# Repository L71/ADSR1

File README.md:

ADSR1
=====

Eurorack digitally controlled ADSR envelope generator.

*** Deprecated (for now at least). 
It works more or less as intended on a breadboard but it got replaced by the ADSR2 module which does more or less the same things but with no MCU.

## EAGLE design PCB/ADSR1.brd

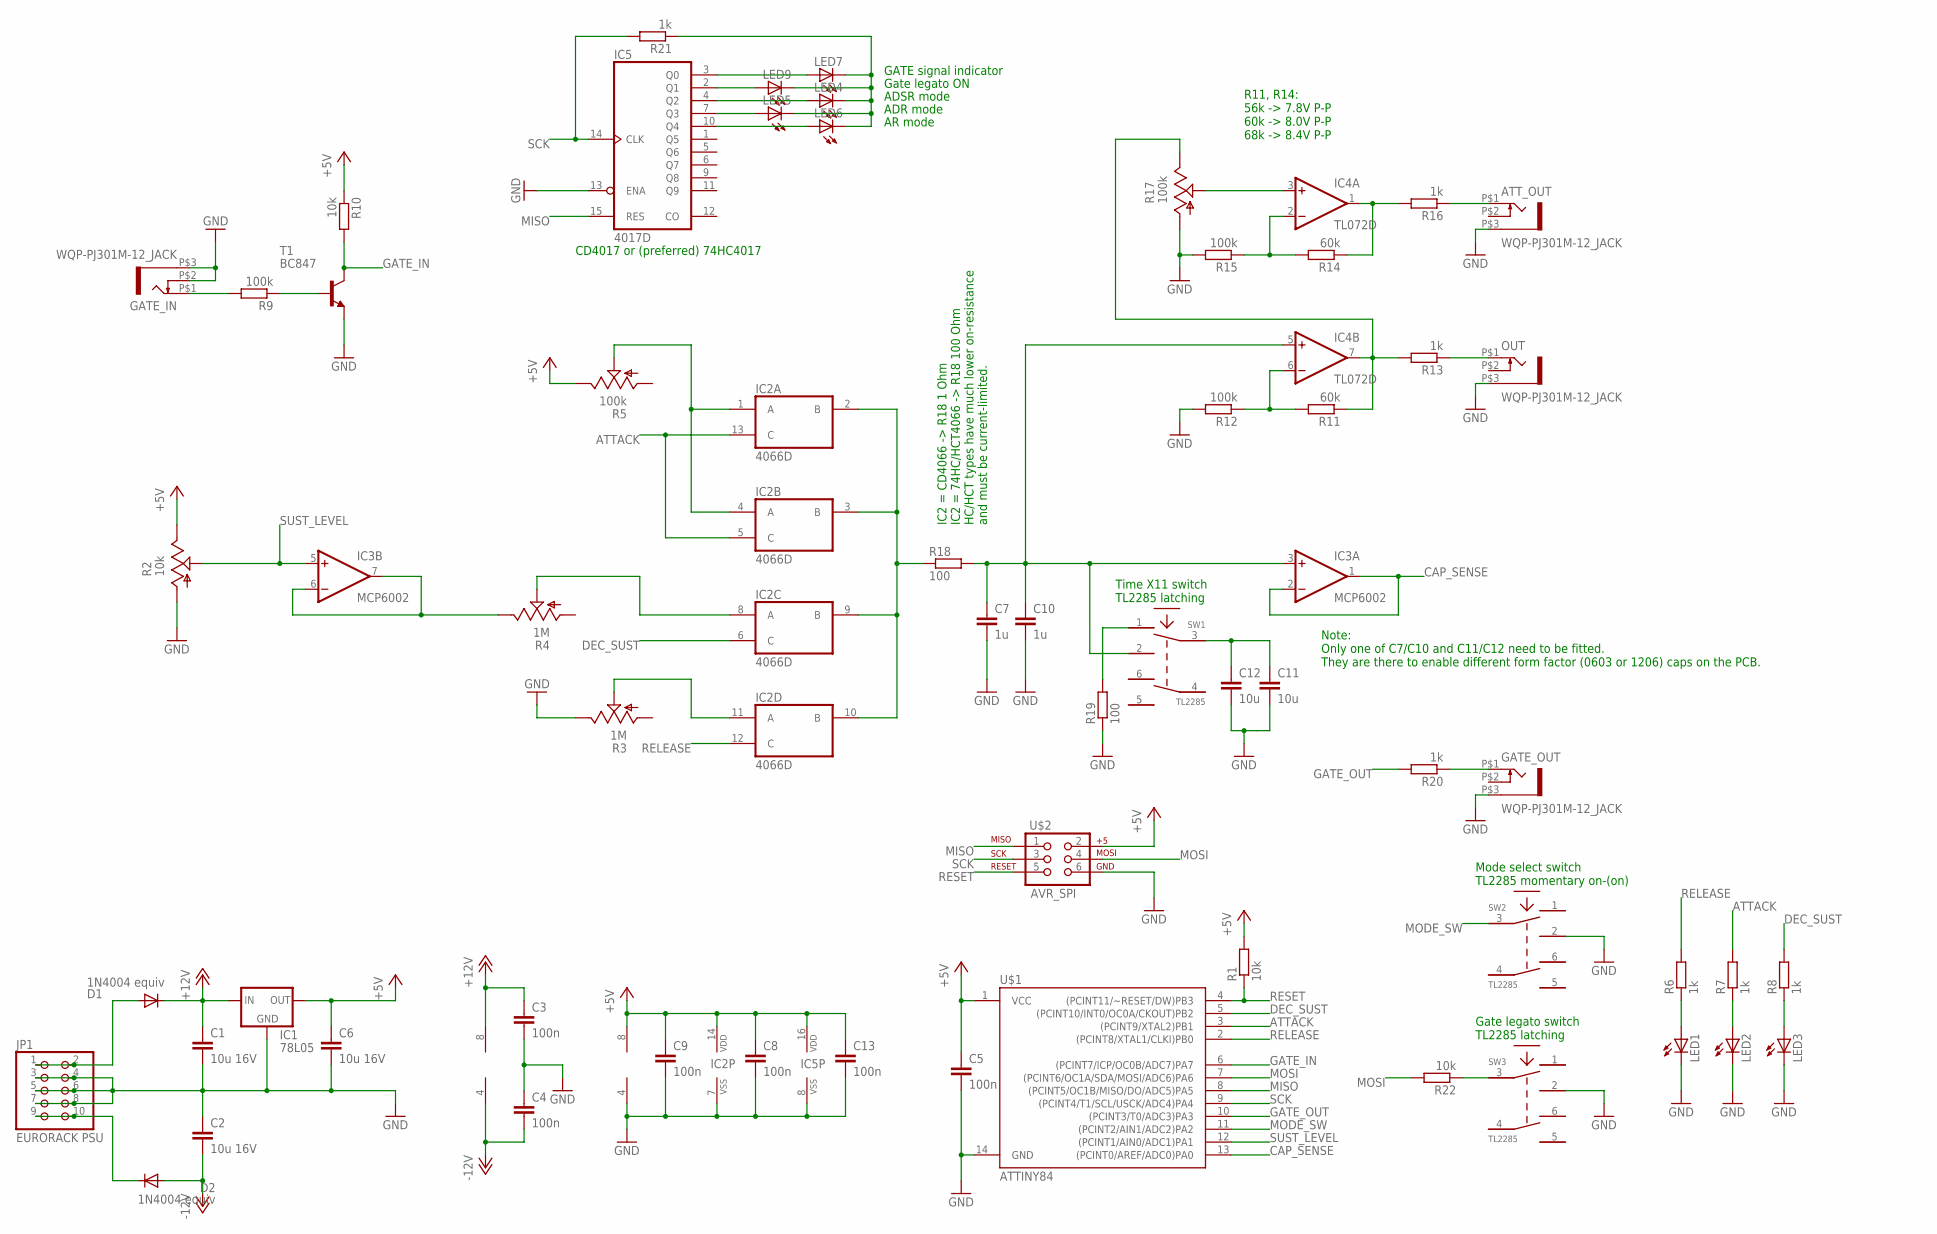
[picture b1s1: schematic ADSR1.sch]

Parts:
ATT_OUT: WQP-PJ301M-12_JACK
C1, C2, C6: 10u 16V; C1206K
C3, C4, C5, C8, C9, C13: 100n; C0603K
C7: 1u; C0603K
C10: 1u; C1206K
C11: 10u; C1206K
C12: 10u; C0603K
D1, D2: 1N4004 equiv; DO214AA
GATE_IN: WQP-PJ301M-12_JACK
GATE_OUT: WQP-PJ301M-12_JACK
IC1: 78L05; SOT89R
IC2: 4066D; SO14
IC3: MCP6002; SO08
IC4: TL072D; SO08
IC5: 4017D; SO16
JP1: EURORACK PSU; 2X05
LED1, LED2, LED3, LED4, LED5, LED6, LED7, LED9: LED3MM
OUT: WQP-PJ301M-12_JACK
R1, R10, R22: 10k; R0603
R2: 10k; ALPS_POT_VERTICAL
R3, R4: 1M; ALPS_POT_VERTICAL
R5, R17: 100k; ALPS_POT_VERTICAL
R6, R7, R8, R13, R16, R20, R21: 1k; R0603
R9, R12, R15: 100k; R0603
R11, R14: 60k; R0603
R18, R19: 100; R1206
SW1, SW2, SW3: TL2285; TL2285_PCB
T1: BC847; SOT23
U$1: ATTINY84; SO14
U$2: AVR_SPI; 2X3

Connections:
+5V: C5.1, C6.1, C8.1, C9.1, C13.1, IC1.PAD1 (OUT), IC2.14 (VDD), IC3.8 (V+), IC5.16 (VDD), R1.2, R2.P$1 (E), R5.P$1 (E), R10.1, U$1.1 (VCC), U$2.2
+12V: C1.1, C3.1, D1.C, IC1.PAD3 (IN), IC4.8 (V+)
-12V: C2.2, C4.2, D2.A, IC4.4 (V-)
ATTACK: IC2.5 (C), IC2.13 (C), R7.2, U$1.3 ((PCINT9/XTAL2)PB1)
CAP_SENSE: IC3.1 (OUT), IC3.2 (-IN), U$1.13 ((PCINT0/AREF/ADC0)PA0)
DEC_SUST: IC2.6 (C), R8.2, U$1.5 ((PCINT10/INT0/OC0A/CKOUT)PB2)
GATE_IN: R10.2, T1.3 (C), U$1.6 ((PCINT7/ICP/OC0B/ADC7)PA7)
GATE_OUT: R20.2, U$1.10 ((PCINT3/T0/ADC3)PA3)
GND: ATT_OUT.P$3 (1), C1.2, C2.1, C3.2, C4.1, C5.2, C6.2, C7.2, C8.2, C9.2, C10.2, C11.2, C12.2, C13.2, GATE_IN.P$2 (3), GATE_IN.P$3 (1), GATE_OUT.P$3 (1), IC1.PAD2 (GND), IC1.PAD4 (GND), IC2.7 (VSS), IC3.4 (V-), IC5.8 (VSS), IC5.13 (ENA), JP1.3, JP1.4, JP1.5, JP1.6, JP1.7, JP1.8, LED1.K (C), LED2.K (C), LED3.K (C), OUT.P$3 (1), R2.P$3 (A), R3.P$1 (E), R12.2, R15.2, R17.P$3 (A), R19.1, SW2.2, SW3.2, T1.2 (E), U$1.14 (GND), U$2.6
MISO: IC5.15 (RES), U$1.8 ((PCINT5/OC1B/MISO/DO/ADC5)PA5), U$2.1
MODE_SW: SW2.3, U$1.11 ((PCINT2/AIN1/ADC2)PA2)
MOSI: R22.2, U$1.7 ((PCINT6/OC1A/SDA/MOSI/ADC6)PA6), U$2.4
unnamed: C7.1, C10.1, IC3.3 (+IN), IC4.5 (+IN), R18.2, SW1.2
unnamed: GATE_IN.P$1 (2), R9.2
unnamed: D1.A, JP1.1, JP1.2
unnamed: LED3.A, R8.1
unnamed: IC2.11 (A), R3.P$2 (S)
unnamed: IC2.8 (A), R4.P$2 (S)
unnamed: IC3.6 (-IN), IC3.7 (OUT), R4.P$1 (E)
unnamed: LED2.A, R7.1
unnamed: LED1.A, R6.1
unnamed: IC2.1 (A), IC2.4 (A), R5.P$2 (S)
unnamed: OUT.P$1 (2), R13.1
unnamed: IC4.6 (-IN), R11.2, R12.1
unnamed: R9.1, T1.1 (B)
unnamed: D2.C, JP1.9, JP1.10
unnamed: IC4.7 (OUT), R11.1, R13.2, R17.P$1 (E)
unnamed: C11.1, C12.1, SW1.3
unnamed: IC2.2 (B), IC2.3 (B), IC2.9 (B), IC2.10 (B), R18.1
unnamed: R19.2, SW1.1
unnamed: ATT_OUT.P$1 (2), R16.1
unnamed: IC4.1 (OUT), R14.1, R16.2
unnamed: IC4.2 (-IN), R14.2, R15.1
unnamed: IC5.2 (Q1), LED9.A
unnamed: GATE_OUT.P$1 (2), R20.1
unnamed: IC4.3 (+IN), R17.P$2 (S)
unnamed: IC5.4 (Q2), LED4.A
unnamed: IC5.7 (Q3), LED5.A
unnamed: IC5.10 (Q4), LED6.A
unnamed: LED4.K (C), LED5.K (C), LED6.K (C), LED7.K (C), LED9.K (C), R21.1
unnamed: IC5.3 (Q0), LED7.A
unnamed: R22.1, SW3.3
RELEASE: IC2.12 (C), R6.2, U$1.2 ((PCINT8/XTAL1/CLKI)PB0)
RESET: R1.1, U$1.4 ((PCINT11/~RESET/DW)PB3), U$2.5
SCK: IC5.14 (CLK), R21.2, U$1.9 ((PCINT4/T1/SCL/USCK/ADC4)PA4), U$2.3
SUST_LEVEL: IC3.5 (+IN), R2.P$2 (S), U$1.12 ((PCINT1/AIN0/ADC1)PA1)

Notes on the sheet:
R11, R14: 56k -> 7.8V P-P 60k -> 8.0V P-P 68k -> 8.4V P-P
Time X11 switch TL2285 latching
IC2 = CD4066 -> R18 1 Ohm IC2 = 74HC/HCT4066 -> R18 100 Ohm HC/HCT types have much lower on-resistance and must be current-limited.
Note: Only one of C7/C10 and C11/C12 need to be fitted. They are there to enable different form factor (0603 or 1206) caps on the PCB.
Mode select switch TL2285 momentary on-(on)
GATE signal indicator
ADSR mode
ADR mode
AR mode
CD4017 or (preferred) 74HC4017
Gate legato switch TL2285 latching
Gate legato ON

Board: 2 copper layers, 61 parts (0 on the bottom side), 46 nets, no tracks yet.

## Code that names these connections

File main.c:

#define F_CPU 8000000UL

#include <avr/io.h>
#include <util/delay.h>
#include <avr/interrupt.h>

#include "env.h"

int main() {

	// IO configuration:
	// PB0, PB1, PB2:	envelope capacitor switches (active: 1)
	// PA7:				gate signal input (active: 0)
	// PA0, PA1:		ADC inputs, capacitor level and sustain level.
	// PA2:				mode selection push button input (with pull-up)
	// PA3:				gate signal output (processed)
	// PA4/SCK:			clock out for UI counter ship
	// PA5/MISO:		reset out for UI counter chip
	// PA6/MOSI:		gate legato switch input

	// output pins for analog switches 
	DDRB |= _BV(PB0) | _BV(PB1) | _BV(PB2);

	// output pin for gate signal, UI chip clock, UI chip reset
	DDRA |= _BV(PA3) | _BV(PA4) | _BV(PA5);
	
	// activate input pull-up on PA2 (mode switch) and PA6 (gate legato switch):
	PORTA |= _BV(PA2) | _BV(PA6);

	// set envelope in relase/off state initially
	sw_set_release();
	
	pc_int_setup();
	adc_setup();
	run_main_timer();



	// light show! =)
	uint8_t x,y;
	for (x=0 ; x<3 ; x++) {
		PORTA |= _BV(PA5);
		PORTA &= ~_BV(PA5);
		for (y=0 ; y<5 ; y++) {
			if (y > 0) {
				PORTA |= _BV(PA4);
				PORTA &= ~_BV(PA4);
			}
			_delay_ms(100);
		}
	}
	
	// reset UI counter chip
	PORTA |= _BV(PA5);
	PORTA &= ~_BV(PA5);
	PORTA |= _BV(PA4);

    // Enable interrupts for all. GO! =)
    SREG |= 0x80 ;
	
    // main loop
    while ( 1 )  {
		// OCR0A = 0;
		// PORTA |= 0b10000000;
        _delay_ms(250);
		// OCR0A = 255;
		// PORTA &= 0b01111111;
		_delay_ms(250);
    }
  
}

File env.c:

// main application 

#include <avr/io.h>
#include <avr/interrupt.h>


// ADC latest values
struct adc_data {
	uint8_t cap_level, sust_level ;
} adc ;

// state machine tracking
#define RELEASING	1
#define ATTACKING	2
#define DEC_SUST	3

// gate event flags
uint8_t gate_went_high=0 ;	// event: gate went high
uint8_t gate_went_low=0 ;	// event: gate went low

// at which ADC/capacitor level the attack phase should be considered done
#define ATTACK_DONE_LVL  254	

// user interface LEDs bit register
uint8_t ui_led_bits=0b00000000;
#define GATE_LED 			0x01			// b0:	gate indicator
#define GATE_LEGATO_LED 	0x02			// b1:	gate legato on/off
#define ADSR_LED 			0x04			// b2:	ADSR mode
#define ADR_LED 			0x08			// b3:	ADR mode	(attack->decay to sustain level->release)
#define ASR_LED				0x10			// b4:	A(S)R mode 	(attack->sustain level->release)
#define NR_LED_BITS			5				// this number of LEDs 

// configure AD converter
void adc_setup() {
	// enable ADC, clock prescaler = /64
	ADCSRA |= (1<<ADEN) | (1<<ADPS2) | (1<<ADPS0) ;
	// left adjust result, we'll use 8 bits results in high byte only.
	ADCSRB |= (1<<ADLAR);
	// disable digital IO on used ADC pins
	DIDR0 = 0b00000011;	
	// Go! =)
	ADCSRA |= (1<<ADSC) ;
}

// start main timer
void run_main_timer() {	// enable 16bit timer1 + interrupts
	OCR1AH = 0x03; // 8MHz, divider 1000 -> 8KHz timer
	OCR1AL = 0xe8;
	// clear on OCR1A, clock prescaler 1. 
	TCCR1B |= (1<<WGM12) | (1<<CS10) ;
	// enable OCR1A interrupt
	TIMSK1 |= (1<<OCIE1A);
}

// functions to manage the 74HC4066 switches for the envelope stages
// only ONE of three must be enabled at once.
inline void sw_set_release() {
	PORTB &= 0xf8;	// all switches off
	PORTB |= _BV(PB0);	
}
inline void sw_set_attack() {
	PORTB &= 0xf8;	// all switches off
	PORTB |= _BV(PB1);
}
inline void sw_set_dec_sust() {
	PORTB &= 0xf8;	// all switches off
	PORTB |= _BV(PB2);
}


// GATE signal handling & interrupt
// 
// setup pin change interrupt
void pc_int_setup() {
	GIMSK |= _BV(PCIE0) ;	// enable pin change 0 interrupt 
	PCMSK0 |= _BV(PCINT7); // enable pin change interrupts for PA7.
}

// update IO and states when gate status changes
inline void set_gate_high() {
	gate_went_high = 1 ;
	ui_led_bits |= GATE_LED;
	PORTA |= _BV(PA3);
}

inline void set_gate_low() {
	gate_went_low = 1;
	ui_led_bits &= ~GATE_LED;
	PORTA &= ~_BV(PA3);
}

ISR(PCINT0_vect) {  	// GATE IN pin change interrupt

	uint8_t gate ; // gate input value
	gate = ( ~PINA & 0x80 );	// check gate input pin

	// clear gate change flags
	gate_went_high=0;
	gate_went_low=0;

	if (gate) {
		set_gate_high();
	} 
	if (! gate) {
		set_gate_low();
	}
	
}


// main envelope state machine
inline void state_update() {

	static uint8_t stage = RELEASING ; 	// curremt ENV stage
	
	// state machine 
	switch (stage) {
	
		case RELEASING:
			if (gate_went_high) {	// act on activated gate signal
				stage = ATTACKING;
				sw_set_attack();
			}
			break;
			
		case ATTACKING:
			// capacitor level reached limit? -> go to decay/sustain
			if (adc.cap_level >= ATTACK_DONE_LVL) {
				stage = DEC_SUST;
				sw_set_dec_sust();
			}
			// gate went low while attacking? -> go to release
			if (gate_went_low) {
				stage = RELEASING;
				sw_set_release();
			}
			break;
			
		case DEC_SUST:
			// gate went low in decay/sustain? -> go to release
			if (gate_went_low) {
				stage = RELEASING;
				sw_set_release();
			}
			if (gate_went_high) {	// act on activated gate signal -> attack phase
				stage = ATTACKING;
				sw_set_attack();
			}
			break;
			
	}
	// clear gate change flags
	gate_went_high=0;
	gate_went_low=0;
}

// reset and update ui led driver/counter chip
void update_ui_leds() {
	// PA4/SCK:			clock out for UI counter ship
	// PA5/MISO:		reset out for UI counter chip
	static uint8_t seq=0;
	
	PORTA &= ~_BV(PA4);	// make sure CLK is low
	
	if (seq == 0) {	// start at 0: reset counter chip
		PORTA |= _BV(PA4);	// PA4 high, make sure LED is off from start
		PORTA |= _BV(PA5);	// send reset pulse... 
		PORTA &= ~_BV(PA5);	// ...
	}
	if (seq > 0) {
		PORTA |= _BV(PA4);	// if not on first bit, pulse counter, next LED
	}
	
	if ( ui_led_bits & (1<<seq)) {	// check if this LED bit is 1? 
		PORTA &= ~_BV(PA4);  		// if so, set PA4 low -> LED lights up
	} 
	seq++;
	if (seq == NR_LED_BITS) {	
		seq=0;
	}
	if (PINA & _BV(PA6)) {
		ui_led_bits |= 0x10;
	} else {
		ui_led_bits &= ~0x10;
	}
}


ISR(TIM1_COMPA_vect) {
	
	static uint8_t adc_chan=0;

	
	uint8_t chan_mask=0x01; // use 2 channels (0-1).
	uint8_t adc_in = ADCH;	// read 8 MSB of ACD results (8 bit resolution used)
	
	switch (adc_chan) {
		case 0 :	// chan 0, current envelope capapcitor level
			adc.cap_level = adc_in;
			break;
		case 1 :	// chan 1, currently set sustain level
			adc.sust_level = adc_in;
			break;

	}

	// next channel...
	adc_chan = ((adc_chan+1) & chan_mask ) ;
	
	// update ADMUX register
	ADMUX &= 0xf0;	// reset channel bits
	ADMUX |= adc_chan ;
	
	// update ENV state machine 
	state_update();
	
	update_ui_leds();
	
	// start next conversion
	ADCSRA |= (1<<ADSC) ;

}

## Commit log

2015-06-27 Initial upload of working basic version.
2015-06-27 Use AVR pin change interrupt to handle the gate signals (PA7).
2015-06-27 Don't trigger next AD conversion until state machine update is done.
2015-06-27 Initial upload of board and schematics.
2015-06-27 Some cleanup of comments etc. Inlined some functions.
2015-06-27 Value adjustments for timing capacitors. Added forgotten diode in -12V supply.
2015-06-28 Added handling of 74HC4017 counter chip that manages the UI LEDs. Added same chip to schematic.
2015-07-12 More or less working breadboard prototype. Will probably not do more with this in a while (if ever).

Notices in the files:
parts and their libraries:
SparkFun-DigitalIC: Licensing: Creative Commons ShareAlike 4.0 International - https://creativecommons.org/licenses/by-sa/4.0
